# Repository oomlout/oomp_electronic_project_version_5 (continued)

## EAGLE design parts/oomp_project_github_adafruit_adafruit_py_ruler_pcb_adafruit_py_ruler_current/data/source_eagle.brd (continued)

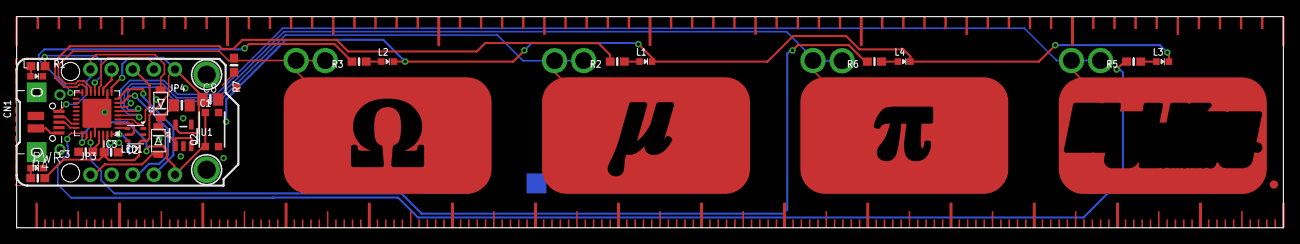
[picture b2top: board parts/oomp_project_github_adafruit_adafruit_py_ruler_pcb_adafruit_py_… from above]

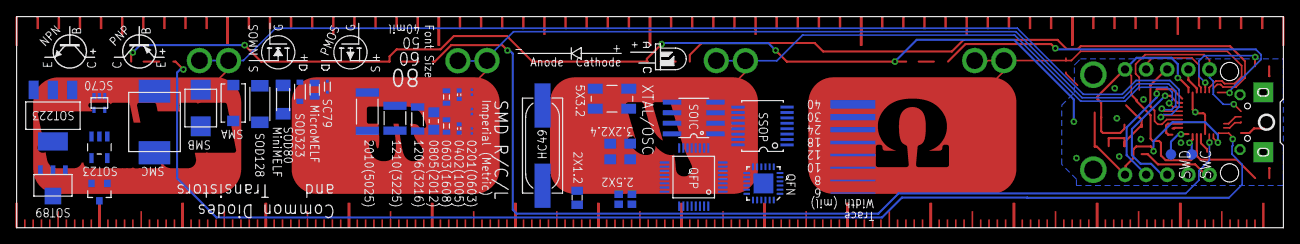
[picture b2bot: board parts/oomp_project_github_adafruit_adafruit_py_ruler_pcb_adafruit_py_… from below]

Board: 2 copper layers, 152.4 x 25.4 mm, 96 parts (43 on the bottom side), 30 nets.

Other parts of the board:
E$1, E$2, E$3, E$4, E$5, E$6, E$7, E$8, E$9, E$10, E$11, E$12, E$13, E$14, E$15: EDGE-MILLIMETERS
E$16, E$60, E$63: 0201
E$17, E$18, E$19, E$20, E$21, E$22: EDGE-INCHES-TENTH
E$23, E$61: 0402
E$24, E$62: 0603
E$25: 0805
E$26: 1206
E$27: 1210
E$28: 2010
E$31: SOT223
E$32: SOT89
E$33: SOT23-5
E$34: SOT23-3
E$35: SC70
E$36: CRYSTAL-SMD-5X3.2
E$37: CRYSTAL-SMD-3.2X2.5
E$38: CRYSTAL-SMD-2.5X2
E$39: HC49UP
E$40: XTAL-2X1.2
E$41: MICROMELF-R
E$42: SC79_INFINEON
E$43: SMA-DIODE
E$44: SMB-DIODE
E$45: SMC
E$47: SOD-128
E$48: SOD-323
E$49: SOD80C
E$50: NMOS-SYMB
E$51: PMOS-SYMB
E$52: DIODE-SYMB
E$53: LED-GUIDE
E$54: NPN-SYMB
E$55: QFN-24
E$56: TSSOP16
E$57: SO08
E$58: TQFP32-5MM
E$59: PNP-SYMB
U$2: PYRULER_BOTTOM
U$7: PCBFEAT-REV-040
U$14: PYRULER_TOP
U$20: TRINKET_M0_TOP

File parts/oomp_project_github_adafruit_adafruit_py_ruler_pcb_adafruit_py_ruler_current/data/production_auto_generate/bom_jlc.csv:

Comment,Designator,Footprint,LCSC Part #
,"E$16,E$60,E$63",Adafruit_PyRuler-import-fps:0201,
,"E$23,E$61",Adafruit_PyRuler-import-fps:0402,
,"E$24,E$62",Adafruit_PyRuler-import-fps:0603,
,E$25,Adafruit_PyRuler-import-fps:0805,
,E$26,Adafruit_PyRuler-import-fps:1206,
,E$27,Adafruit_PyRuler-import-fps:1210,
,"JP3,JP4",Adafruit_PyRuler-import-fps:1X05_ROUND_70,C42431835
,E$28,Adafruit_PyRuler-import-fps:2010,
,E$38,Adafruit_PyRuler-import-fps:CRYSTAL-SMD-2.5X2,
,E$37,Adafruit_PyRuler-import-fps:CRYSTAL-SMD-3.2X2.5,
,E$36,Adafruit_PyRuler-import-fps:CRYSTAL-SMD-5X3.2,
,E$52,Adafruit_PyRuler-import-fps:DIODE-SYMB,
,"E$17,E$18,E$19,E$20,E$21,E$22",Adafruit_PyRuler-import-fps:EDGE-INCHES-TENTH,
,"E$1,E$2,E$3,E$4,E$5,E$6,E$7,E$8,E$9,E$10,E$11,E$12,E$13,E$14,E$15",Adafruit_PyRuler-import-fps:EDGE-MILLIMETERS,
,E$39,Adafruit_PyRuler-import-fps:HC49UP,
,E$53,Adafruit_PyRuler-import-fps:LED-GUIDE,
,E$41,Adafruit_PyRuler-import-fps:MICROMELF-R,
,E$50,Adafruit_PyRuler-import-fps:NMOS-SYMB,
,E$54,Adafruit_PyRuler-import-fps:NPN-SYMB,
,U$7,Adafruit_PyRuler-import-fps:PCBFEAT-REV-040,
,E$51,Adafruit_PyRuler-import-fps:PMOS-SYMB,
,E$59,Adafruit_PyRuler-import-fps:PNP-SYMB,
,U$2,Adafruit_PyRuler-import-fps:PYRULER_BOTTOM,
,U$14,Adafruit_PyRuler-import-fps:PYRULER_TOP,
,E$55,Adafruit_PyRuler-import-fps:QFN-24,
,E$35,Adafruit_PyRuler-import-fps:SC70,
,E$42,Adafruit_PyRuler-import-fps:SC79_INFINEON,
,E$43,Adafruit_PyRuler-import-fps:SMA-DIODE,
,E$44,Adafruit_PyRuler-import-fps:SMB-DIODE,
,E$45,Adafruit_PyRuler-import-fps:SMC,
,E$57,Adafruit_PyRuler-import-fps:SO08,
,E$47,Adafruit_PyRuler-import-fps:SOD-128,
,E$48,Adafruit_PyRuler-import-fps:SOD-323,
,E$49,Adafruit_PyRuler-import-fps:SOD80C,
,E$31,Adafruit_PyRuler-import-fps:SOT223,
,E$34,Adafruit_PyRuler-import-fps:SOT23-3,
,E$33,Adafruit_PyRuler-import-fps:SOT23-5,
,E$32,Adafruit_PyRuler-import-fps:SOT89,
,E$58,Adafruit_PyRuler-import-fps:TQFP32-5MM,
,U$20,Adafruit_PyRuler-import-fps:TRINKET_M0_TOP,
,E$56,Adafruit_PyRuler-import-fps:TSSOP16,
,E$40,Adafruit_PyRuler-import-fps:XTAL-2X1.2,
10K,"R4,R5,R6",Adafruit_PyRuler-import-fps:0603-NO,C98220
10uF,"C1,C8",Adafruit_PyRuler-import-fps:0805-NO,
1uF,"C2,C3",Adafruit_PyRuler-import-fps:0603-NO,C5673
2.2K,"R1,R2,R3",Adafruit_PyRuler-import-fps:0603-NO,C4190
2M,R7,Adafruit_PyRuler-import-fps:0603-NO,
4U#20329,CN1,Adafruit_PyRuler-import-fps:4UCONN_20329_NARROW,
AP102-2020,LED1,Adafruit_PyRuler-import-fps:APA102_2020,
AP2112K-3.3,U1,Adafruit_PyRuler-import-fps:SOT23-5,
ATSAMD21E,IC3,Adafruit_PyRuler-import-fps:QFN32_5MM,
blue,L3,Adafruit_PyRuler-import-fps:CHIPLED_0603_NOOUTLINE,
FIDUCIAL_1MM,"U$1,U$6",Adafruit_PyRuler-import-fps:FIDUCIAL_1MM,
green,"L4,PWR0",Adafruit_PyRuler-import-fps:CHIPLED_0603_NOOUTLINE,
red,"L0,L2",Adafruit_PyRuler-import-fps:CHIPLED_0603_NOOUTLINE,
reset,Q2,Adafruit_PyRuler-import-fps:BTN_KMR2_4.6X2.8,
SCHOTTKY,"D2,D3",Adafruit_PyRuler-import-fps:SOD-123FL,
"TPB1,27","SWC0,SWD0","Adafruit_PyRuler-import-fps:B1,27",
yellow,L1,Adafruit_PyRuler-import-fps:CHIPLED_0603_NOOUTLINE,

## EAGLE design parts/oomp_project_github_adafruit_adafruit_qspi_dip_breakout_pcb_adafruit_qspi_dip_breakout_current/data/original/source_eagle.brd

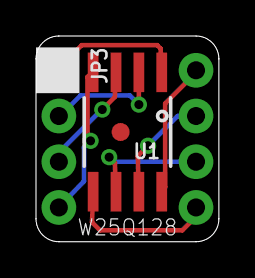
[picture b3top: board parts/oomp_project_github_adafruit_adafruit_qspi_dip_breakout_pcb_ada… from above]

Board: 2 copper layers, 10.2 x 11.4 mm, 5 parts (1 on the bottom side), 8 nets.

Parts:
FID1: FIDUCIAL_1MM
JP2, JP3: 1X04_ROUND_76
U1: GENERIC QSPI; SOIC8_208MIL
U$4: ADAFRUIT_2.5MM

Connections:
3.3V: JP2.1, U1.8
GND: JP3.4, U1.4
IO2: JP3.3, U1.3
IO3: JP2.2, U1.7
MISO: JP3.2, U1.2
MOSI: JP2.4, U1.5
SCK: JP2.3, U1.6
SS: JP3.1, U1.1

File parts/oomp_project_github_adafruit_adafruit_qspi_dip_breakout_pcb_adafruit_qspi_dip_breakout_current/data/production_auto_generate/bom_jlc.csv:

Comment,Designator,Footprint,LCSC Part #
,"JP2,JP3",Adafruit QSPI DIP Breakout-import-fps:1X04_ROUND_76,C42431795
,U$4,Adafruit QSPI DIP Breakout-import-fps:ADAFRUIT_2.5MM,
GENERIC QSPI,U1,Adafruit QSPI DIP Breakout-import-fps:SOIC8_208MIL,

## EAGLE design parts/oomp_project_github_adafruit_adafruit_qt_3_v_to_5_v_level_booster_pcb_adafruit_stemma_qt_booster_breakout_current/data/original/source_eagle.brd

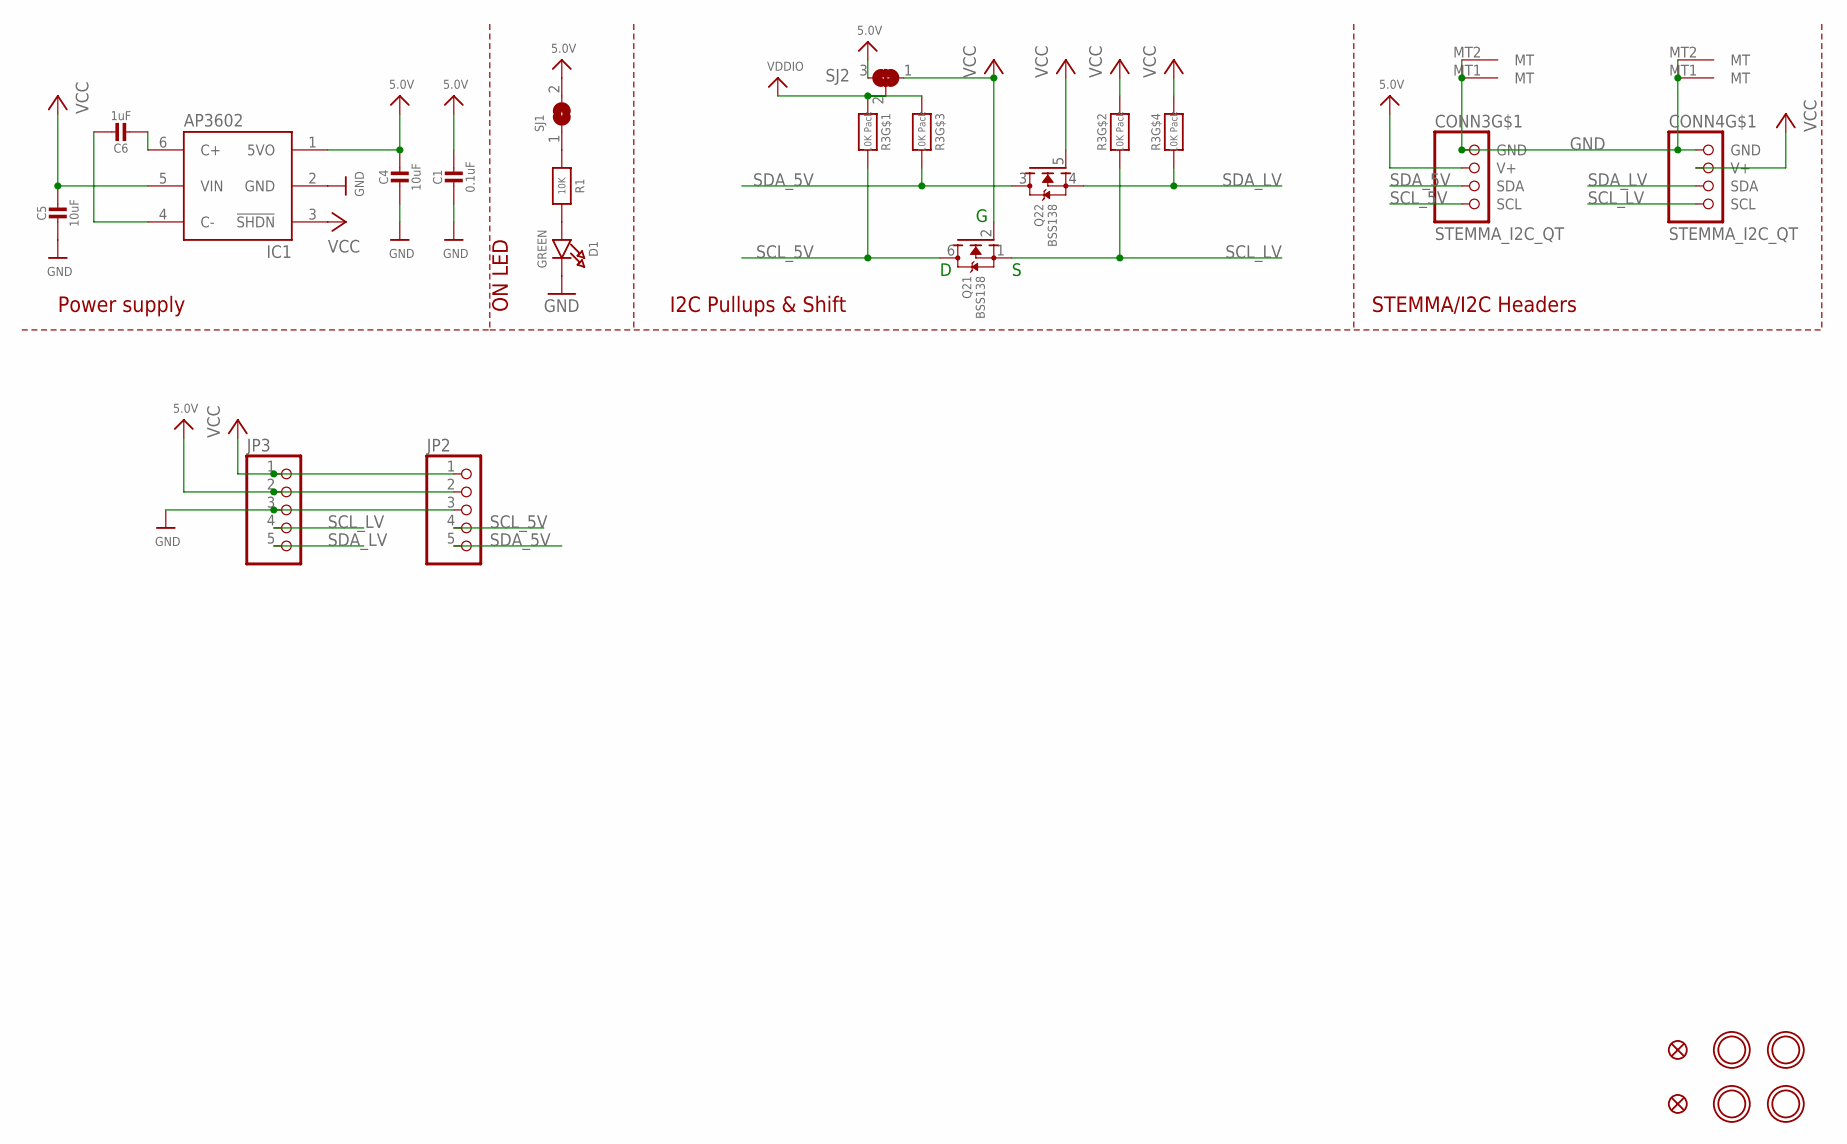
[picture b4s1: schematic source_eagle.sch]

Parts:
C1: 0.1uF; 0603-NO
C4, C5: 10uF; 0805-NO
C6: 1uF; 0805-NO
CONN3, CONN4: STEMMA_I2C_QT; JST_SH4
D1: GREEN; CHIPLED_0603_NOOUTLINE
FID3, FID4: FIDUCIAL_1MM
IC1: AP3602/RT9361; SOT23-6
JP2, JP3: HEADER-1X576MIL; 1X05_ROUND_76
Q2: BSS138; SOT363
R1: 10K; 0603-NO
R3: 10K Pack; RESPACK_4X0603
SJ1: SOLDERJUMPERCLOSED; SOLDERJUMPER_CLOSEDWIRE
SJ2: SOLDERJUMPER_2WAY; SOLDERJUMPER_2WAY_OPEN_NOPASTE
U$1, U$17, U$19, U$21: MOUNTINGHOLE2.5; MOUNTINGHOLE_2.5_PLATED

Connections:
5.0V: C1.1, C4.1, CONN3.2 (V+), IC1.1 (5VO), JP2.2, JP3.2, SJ1.2, SJ2.3
GND: C1.2, C4.2, C5.2, CONN3.1 (GND), CONN3.MT1 (MT), CONN3.MT2 (MT), CONN4.1 (GND), CONN4.MT1 (MT), CONN4.MT2 (MT), D1.C, IC1.2 (GND), JP2.3, JP3.3
unnamed: D1.A, R1.2
unnamed: R1.1, SJ1.1
unnamed: C6.2, IC1.6 (C+)
unnamed: C6.1, IC1.4 (C-)
SCL_5V: CONN3.4 (SCL), JP2.4, Q2.6 (D), R3.8 (2)
SCL_LV: CONN4.4 (SCL), JP3.4, Q2.1 (S), R3.7 (2)
SDA_5V: CONN3.3 (SDA), JP2.5, Q2.3 (D), R3.6 (2)
SDA_LV: CONN4.3 (SDA), JP3.5, Q2.4 (S), R3.5 (2)
VCC: C5.1, CONN4.2 (V+), IC1.3 (!SHDN), IC1.5 (VIN), JP2.1, JP3.1, Q2.2 (G), Q2.5 (G), R3.2 (1), R3.4 (1), SJ2.1
VDDIO: R3.1, R3.3 (1), SJ2.2

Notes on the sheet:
I2C Pullups & Shift
STEMMA/I2C Headers
ON LED
Power supply

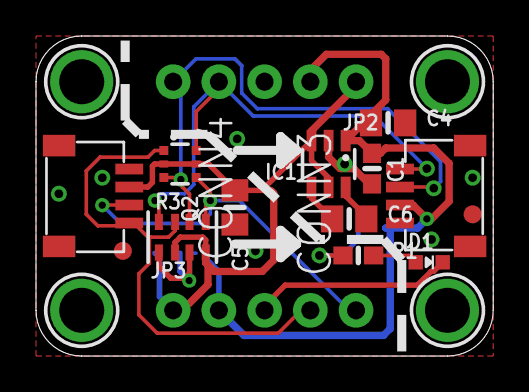
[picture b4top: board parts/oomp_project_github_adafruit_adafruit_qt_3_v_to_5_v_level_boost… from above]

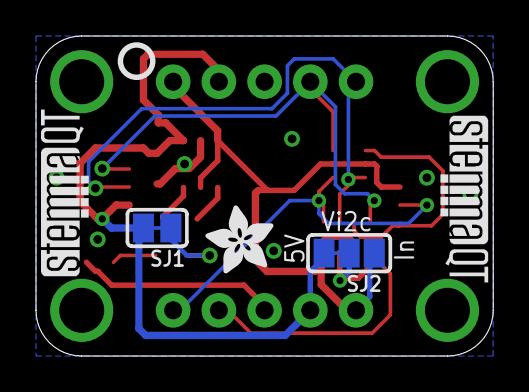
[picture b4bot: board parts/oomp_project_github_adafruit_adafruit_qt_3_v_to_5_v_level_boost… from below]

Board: 2 copper layers, 25.4 x 17.8 mm, 40 parts (8 on the bottom side), 12 nets.

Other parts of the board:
PLABEL0: PLABEL0
PLABEL1: PLABEL1
PLABEL2: PLABEL2
PLABEL3: PLABEL3
PLABEL4: PLABEL4
PLABEL5: PLABEL5
PLABEL6: PLABEL6
PLABEL7: PLABEL7
PLABEL8: PLABEL8
PLABEL9: PLABEL9
PLABEL10: PLABEL10
PLABEL11: PLABEL11
PLABEL12: PLABEL12
PLABEL13: PLABEL13
PLABEL14: PLABEL14
U$2: ADAFRUIT_3.5MM
U$25: PCBFEAT-REV-040
U$30, U$31: STEMMAQT

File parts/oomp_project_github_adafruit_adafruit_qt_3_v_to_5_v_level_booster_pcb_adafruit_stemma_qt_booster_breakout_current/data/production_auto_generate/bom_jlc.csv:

Comment,Designator,Footprint,LCSC Part #
,"JP2,JP3",Adafruit STEMMA QT Booster Breakout-import-fps:1X05_ROUND_76,C42431835
,U$2,Adafruit STEMMA QT Booster Breakout-import-fps:ADAFRUIT_3.5MM,
,U$25,Adafruit STEMMA QT Booster Breakout-import-fps:PCBFEAT-REV-040,
,PLABEL0,Adafruit STEMMA QT Booster Breakout-import-fps:PLABEL0,
,PLABEL1,Adafruit STEMMA QT Booster Breakout-import-fps:PLABEL1,
,PLABEL10,Adafruit STEMMA QT Booster Breakout-import-fps:PLABEL10,
,PLABEL11,Adafruit STEMMA QT Booster Breakout-import-fps:PLABEL11,
,PLABEL12,Adafruit STEMMA QT Booster Breakout-import-fps:PLABEL12,
,PLABEL13,Adafruit STEMMA QT Booster Breakout-import-fps:PLABEL13,
,PLABEL14,Adafruit STEMMA QT Booster Breakout-import-fps:PLABEL14,
,PLABEL2,Adafruit STEMMA QT Booster Breakout-import-fps:PLABEL2,
,PLABEL3,Adafruit STEMMA QT Booster Breakout-import-fps:PLABEL3,
,PLABEL4,Adafruit STEMMA QT Booster Breakout-import-fps:PLABEL4,
,PLABEL5,Adafruit STEMMA QT Booster Breakout-import-fps:PLABEL5,
,PLABEL6,Adafruit STEMMA QT Booster Breakout-import-fps:PLABEL6,
,PLABEL7,Adafruit STEMMA QT Booster Breakout-import-fps:PLABEL7,
,PLABEL8,Adafruit STEMMA QT Booster Breakout-import-fps:PLABEL8,
,PLABEL9,Adafruit STEMMA QT Booster Breakout-import-fps:PLABEL9,
,"U$30,U$31",Adafruit STEMMA QT Booster Breakout-import-fps:STEMMAQT,
0.1uF,C1,Adafruit STEMMA QT Booster Breakout-import-fps:0603-NO,C14663
10K,R1,Adafruit STEMMA QT Booster Breakout-import-fps:0603-NO,C98220
10K Pack,R3,Adafruit STEMMA QT Booster Breakout-import-fps:RESPACK_4X0603,C98220
10uF,"C4,C5",Adafruit STEMMA QT Booster Breakout-import-fps:0805-NO,
1uF,C6,Adafruit STEMMA QT Booster Breakout-import-fps:0805-NO,
AP3602/RT9361,IC1,Adafruit STEMMA QT Booster Breakout-import-fps:SOT23-6,
BSS138,Q2,Adafruit STEMMA QT Booster Breakout-import-fps:SOT363,
GREEN,D1,Adafruit STEMMA QT Booster Breakout-import-fps:CHIPLED_0603_NOOUTLINE,
STEMMA_I2C_QT,"CONN3,CONN4",Adafruit STEMMA QT Booster Breakout-import-fps:JST_SH4,C160404

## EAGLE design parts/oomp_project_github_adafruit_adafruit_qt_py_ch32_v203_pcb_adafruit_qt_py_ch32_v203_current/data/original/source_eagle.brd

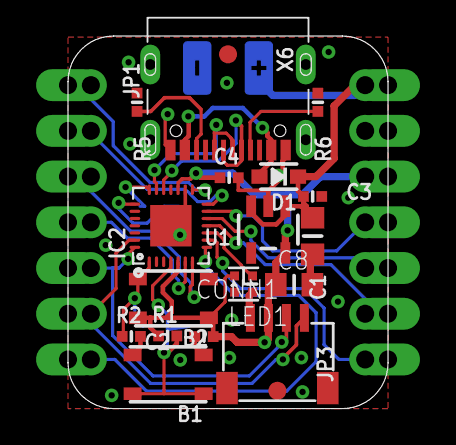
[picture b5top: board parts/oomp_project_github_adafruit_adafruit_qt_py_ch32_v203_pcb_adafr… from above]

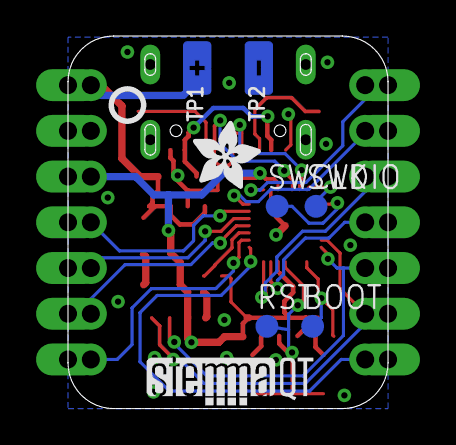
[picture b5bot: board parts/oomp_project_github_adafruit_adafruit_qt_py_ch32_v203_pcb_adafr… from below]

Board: 2 copper layers, 17.8 x 20.7 mm, 48 parts (26 on the bottom side), 24 nets.

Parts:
B1: BTN_RST; BTN_RKB2_4.6X2.8
B2: BTN_BOOT; BTN_RKB2_4.6X2.8
BOOT: TPB1,27; B1,27
C1, C8: 10uF; _0805MP
C2, C3, C4: 1uF; _0402NO
CONN1: STEMMA_I2C_QTSKINNY; JST_SH4_SKINNY
D1: NSR0320; SOD-323_MINI
IC2: CH32V203G6U6_; QFN28_4MM_0.4MM
JP1, JP3: 1X07_CASTEL
LED1: WS2812B_SK6805_1515; SK6805_1515
PLABEL0: PLABEL0
PLABEL1: PLABEL1
PLABEL2: PLABEL2
PLABEL3: PLABEL3
PLABEL4: PLABEL4
PLABEL5: PLABEL5
PLABEL6: PLABEL6
PLABEL7: PLABEL7
PLABEL8: PLABEL8
PLABEL9: PLABEL9
PLABEL10: PLABEL10
PLABEL11: PLABEL11
PLABEL12: PLABEL12
PLABEL13: PLABEL13
PLABEL14: PLABEL14
PLABEL15: PLABEL15
R1, R2: 10K; _0402NO
R5, R6: 5.1K; _0402NO
RST: TPB1,27; B1,27
SWCLK: SWCLK; B1,27
SWDIO: SWDIO; B1,27
TP1: TESTPOINT_PLUS_1X3MM
TP2: TESTPOINT_MINUS_1X3MM
U1: AP2112K-3.3; SOT23-5
U$6, U$8: FIDUCIAL_1MM
U$11: ADAFRUIT_3.5MM
U$12: PCBFEAT-REV-040
U$13: QTPY_CH32V203_BOT
U$21: STEMMAQT
U$23: QTPY_CH32V203_TOP
X6: USB TYPE C; USB_C_CUSB31-CFM2AX-01-X

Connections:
3.3V: B2.A, B2.A', C2.1, C4.1, C8.1, CONN1.2, IC2.5, IC2.17, JP3.5, JP3.5C, LED1.2, R1.1, U1.5
!RESET: B1.A, B1.A', IC2.4, R1.2, RST.TP
+5V: C1.1, C3.1, D1.C, JP3.7, JP3.7C, TP1.P$1, U1.1, U1.3
A0: IC2.15, JP1.1, JP1.1C
A1: IC2.14, JP1.2, JP1.2C
A2: IC2.7, JP1.3, JP1.3C
A3: IC2.6, JP1.4, JP1.4C
BOOT0: B2.B, BOOT.TP, IC2.1, R2.1
CC1: R6.2, X6.A5
CC2: R5.2, X6.B5
D+: IC2.20, X6.A6, X6.B6
D-: IC2.19, X6.A7, X6.B7
GND: B1.B, B1.B', C1.2, C2.2, C3.2, C4.2, C8.2, CONN1.1, CONN1.MT1, CONN1.MT2, IC2.16, IC2.THERMAL, JP3.6, JP3.6C, LED1.4, R2.2, R5.1, R6.1, TP2.P$1, U1.2, X6.A1B12, X6.B1A12
MISO: IC2.12, JP3.3, JP3.3C
MOSI: IC2.13, JP3.4, JP3.4C
NEOPIX: IC2.10, LED1.1
RX: IC2.9, JP3.1, JP3.1C
SCK: IC2.11, JP3.2, JP3.2C
SCL: CONN1.4, IC2.27, JP1.6, JP1.6C
SDA: CONN1.3, IC2.28, JP1.5, JP1.5C
SWC: IC2.22, SWCLK.TP
SWD: IC2.21, SWDIO.TP
TX: IC2.8, JP1.7, JP1.7C
VBUS: D1.A, X6.A4B9, X6.B4A9

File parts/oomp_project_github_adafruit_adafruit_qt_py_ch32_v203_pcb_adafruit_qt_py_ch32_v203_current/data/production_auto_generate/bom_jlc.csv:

Comment,Designator,Footprint,LCSC Part #
,"JP1,JP3",Adafruit QT Py CH32V203-import-fps:1X07_CASTEL,C7501585
,U$11,Adafruit QT Py CH32V203-import-fps:ADAFRUIT_3.5MM,
,U$12,Adafruit QT Py CH32V203-import-fps:PCBFEAT-REV-040,
,PLABEL0,Adafruit QT Py CH32V203-import-fps:PLABEL0,
,PLABEL1,Adafruit QT Py CH32V203-import-fps:PLABEL1,
,PLABEL10,Adafruit QT Py CH32V203-import-fps:PLABEL10,
,PLABEL11,Adafruit QT Py CH32V203-import-fps:PLABEL11,
,PLABEL12,Adafruit QT Py CH32V203-import-fps:PLABEL12,
,PLABEL13,Adafruit QT Py CH32V203-import-fps:PLABEL13,
,PLABEL14,Adafruit QT Py CH32V203-import-fps:PLABEL14,
,PLABEL15,Adafruit QT Py CH32V203-import-fps:PLABEL15,
,PLABEL2,Adafruit QT Py CH32V203-import-fps:PLABEL2,
,PLABEL3,Adafruit QT Py CH32V203-import-fps:PLABEL3,
,PLABEL4,Adafruit QT Py CH32V203-import-fps:PLABEL4,
,PLABEL5,Adafruit QT Py CH32V203-import-fps:PLABEL5,
,PLABEL6,Adafruit QT Py CH32V203-import-fps:PLABEL6,
,PLABEL7,Adafruit QT Py CH32V203-import-fps:PLABEL7,
,PLABEL8,Adafruit QT Py CH32V203-import-fps:PLABEL8,
,PLABEL9,Adafruit QT Py CH32V203-import-fps:PLABEL9,
,U$13,Adafruit QT Py CH32V203-import-fps:QTPY_CH32V203_BOT,
,U$23,Adafruit QT Py CH32V203-import-fps:QTPY_CH32V203_TOP,
,U$21,Adafruit QT Py CH32V203-import-fps:STEMMAQT,
,TP2,Adafruit QT Py CH32V203-import-fps:TESTPOINT_MINUS_1X3MM,
,TP1,Adafruit QT Py CH32V203-import-fps:TESTPOINT_PLUS_1X3MM,
10K,"R1,R2",Adafruit QT Py CH32V203-import-fps:_0402NO,C2906861
10uF,"C1,C8",Adafruit QT Py CH32V203-import-fps:_0805MP,
1uF,"C2,C3,C4",Adafruit QT Py CH32V203-import-fps:_0402NO,C2887021
5.1K,"R5,R6",Adafruit QT Py CH32V203-import-fps:_0402NO,C25905
AP2112K-3.3,U1,Adafruit QT Py CH32V203-import-fps:SOT23-5,
BTN_BOOT,B2,Adafruit QT Py CH32V203-import-fps:BTN_RKB2_4.6X2.8,
BTN_RST,B1,Adafruit QT Py CH32V203-import-fps:BTN_RKB2_4.6X2.8,
CH32V203G6U6_,IC2,Adafruit QT Py CH32V203-import-fps:QFN28_4MM_0.4MM,
FIDUCIAL_1MM,"U$6,U$8",Adafruit QT Py CH32V203-import-fps:FIDUCIAL_1MM,
NSR0320,D1,Adafruit QT Py CH32V203-import-fps:SOD-323_MINI,
STEMMA_I2C_QTSKINNY,CONN1,Adafruit QT Py CH32V203-import-fps:JST_SH4_SKINNY,
SWCLK,SWCLK0,"Adafruit QT Py CH32V203-import-fps:B1,27",
SWDIO,SWDIO0,"Adafruit QT Py CH32V203-import-fps:B1,27",
"TPB1,27","BOOT0,RST0","Adafruit QT Py CH32V203-import-fps:B1,27",
USB TYPE C,X6,Adafruit QT Py CH32V203-import-fps:USB_C_CUSB31-CFM2AX-01-X,
WS2812B_SK6805_1515,LED1,Adafruit QT Py CH32V203-import-fps:SK6805_1515,

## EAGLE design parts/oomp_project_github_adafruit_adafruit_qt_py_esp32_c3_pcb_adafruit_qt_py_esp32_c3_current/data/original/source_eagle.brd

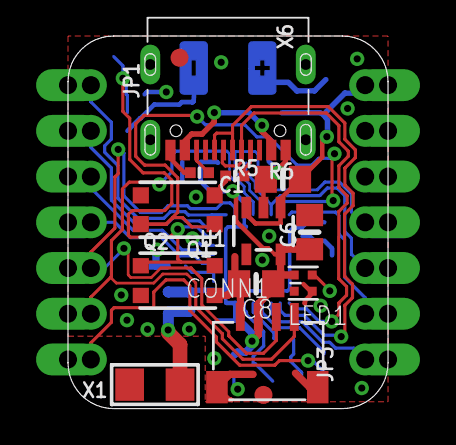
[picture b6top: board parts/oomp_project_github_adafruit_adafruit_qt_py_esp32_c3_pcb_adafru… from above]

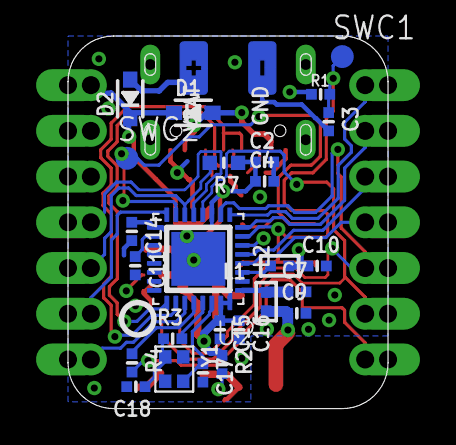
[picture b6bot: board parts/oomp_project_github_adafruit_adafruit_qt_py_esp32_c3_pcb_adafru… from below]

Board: 2 copper layers, 17.8 x 20.7 mm, 46 parts (29 on the bottom side), 31 nets.

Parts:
C1, C6, C8: 22uF; 0805-NO
C2, C3, C11, C15: 1uF; _0402NO
C4, C10, C14: 0.1uF; _0402NO
C7, C9: TBD; _0402NO
C16: 0.01uF; _0402NO
C17, C18: 16pF; _0402NO
CONN1: STEMMA_I2C_QTSKINNY; JST_SH4_SKINNY
D1, D2: NSR0320; SOD-323_MINI
GND: TESTPOINT_MINUS_1X3MM
JP1, JP3: 1X07_CASTEL
L1: 2nH; _0402
L2: 0 ohm; _0402
LED1: WS2812B_SK6805_1515; SK6805_1515
Q1: BOOT0; BTN_KMR2_4.6X2.8
Q2: reset; BTN_KMR2_SLIM
R1, R2: 10K; _0402NO
R3: 0; _0402NO
R4: 1k; _0402NO
R5, R6: 5.1K; _0402NO
R7: 10K; _0603MP_TWO6MIL
SWC1, SWC2: TPB1,27; B1,27
U1: AP2112K-3.3; SOT23-5
U2: ESP32-C3FH4; QFN32_5MM
U$3: QTPYC3_TOP
U$6, U$8: FIDUCIAL_1MM
U$12: PCBFEAT-REV-040
U$18: QTPYC3_BOT
VBAT: TESTPOINT_PLUS_1X3MM
X1: 2.4GHz; ANT_2450AT18B100
X6: USB TYPE C; USB_C_CUSB31-CFM2AX-01-X
Y1: 40MHz; CRYSTAL_2X1.6

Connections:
3.3V: C2.1, C4.1, C6.1, C8.1, C10.1, C14.1, C15.1, C16.1, CONN1.2, JP3.5, JP3.5C, L1.1, LED1.2, R1.1, R2.1, R7.1, U1.5, U2.11, U2.17, U2.31, U2.32
!RESET: C3.1, Q2.A, Q2.A', R1.2, SWC1.TP, U2.7
+5V: C1.1, D1.C, D2.C, JP3.7, JP3.7C, U1.1, U1.3
A0: JP1.1, JP1.1C, U2.9
A1: JP1.2, JP1.2C, U2.8
A2: JP1.3, JP1.3C, U2.5
A3: JP1.4, JP1.4C, U2.4
BOOT: Q1.A, Q1.A', SWC2.TP, U2.15
CC1: R6.2, X6.A5
CC2: R5.2, X6.B5
D+: U2.26, X6.A6, X6.B6
D-: U2.25, X6.A7, X6.B7
GND: C1.2, C2.2, C3.2, C4.2, C6.2, C7.2, C8.2, C9.2, C10.2, C11.2, C14.2, C15.2, C16.2, C17.2, C18.2, CONN1.1, CONN1.MT1, CONN1.MT2, GND.P$1, JP3.6, JP3.6C, LED1.4, Q1.B', Q2.B, Q2.B', R5.1, R6.1, U1.2, U2.33, X6.A1B12, X6.B1A12
LNA: C7.1, L2.2, U2.1
MISO: JP3.3, JP3.3C, R7.2, U2.14
MOSI: JP3.4, JP3.4C, U2.13
unnamed: R4.1, U2.28
unnamed: C9.1, L2.1, X1.FP
unnamed: R3.2, U2.29
unnamed: C17.1, U2.30, Y1.3
unnamed: C18.1, R3.1, Y1.1
NEOPIX: LED1.1, R2.2, U2.6
RX: JP3.1, JP3.1C, U2.27
SCK: JP3.2, JP3.2C, U2.16
SCL: CONN1.4, JP1.6, JP1.6C, U2.12
SDA: CONN1.3, JP1.5, JP1.5C, U2.10
TX: JP1.7, JP1.7C, R4.2
VBAT: D2.A, VBAT.P$1
VBUS: D1.A, X6.A4B9, X6.B4A9
VDD3P3: L1.2, U2.2, U2.3
VDD_SPI: C11.1, U2.18

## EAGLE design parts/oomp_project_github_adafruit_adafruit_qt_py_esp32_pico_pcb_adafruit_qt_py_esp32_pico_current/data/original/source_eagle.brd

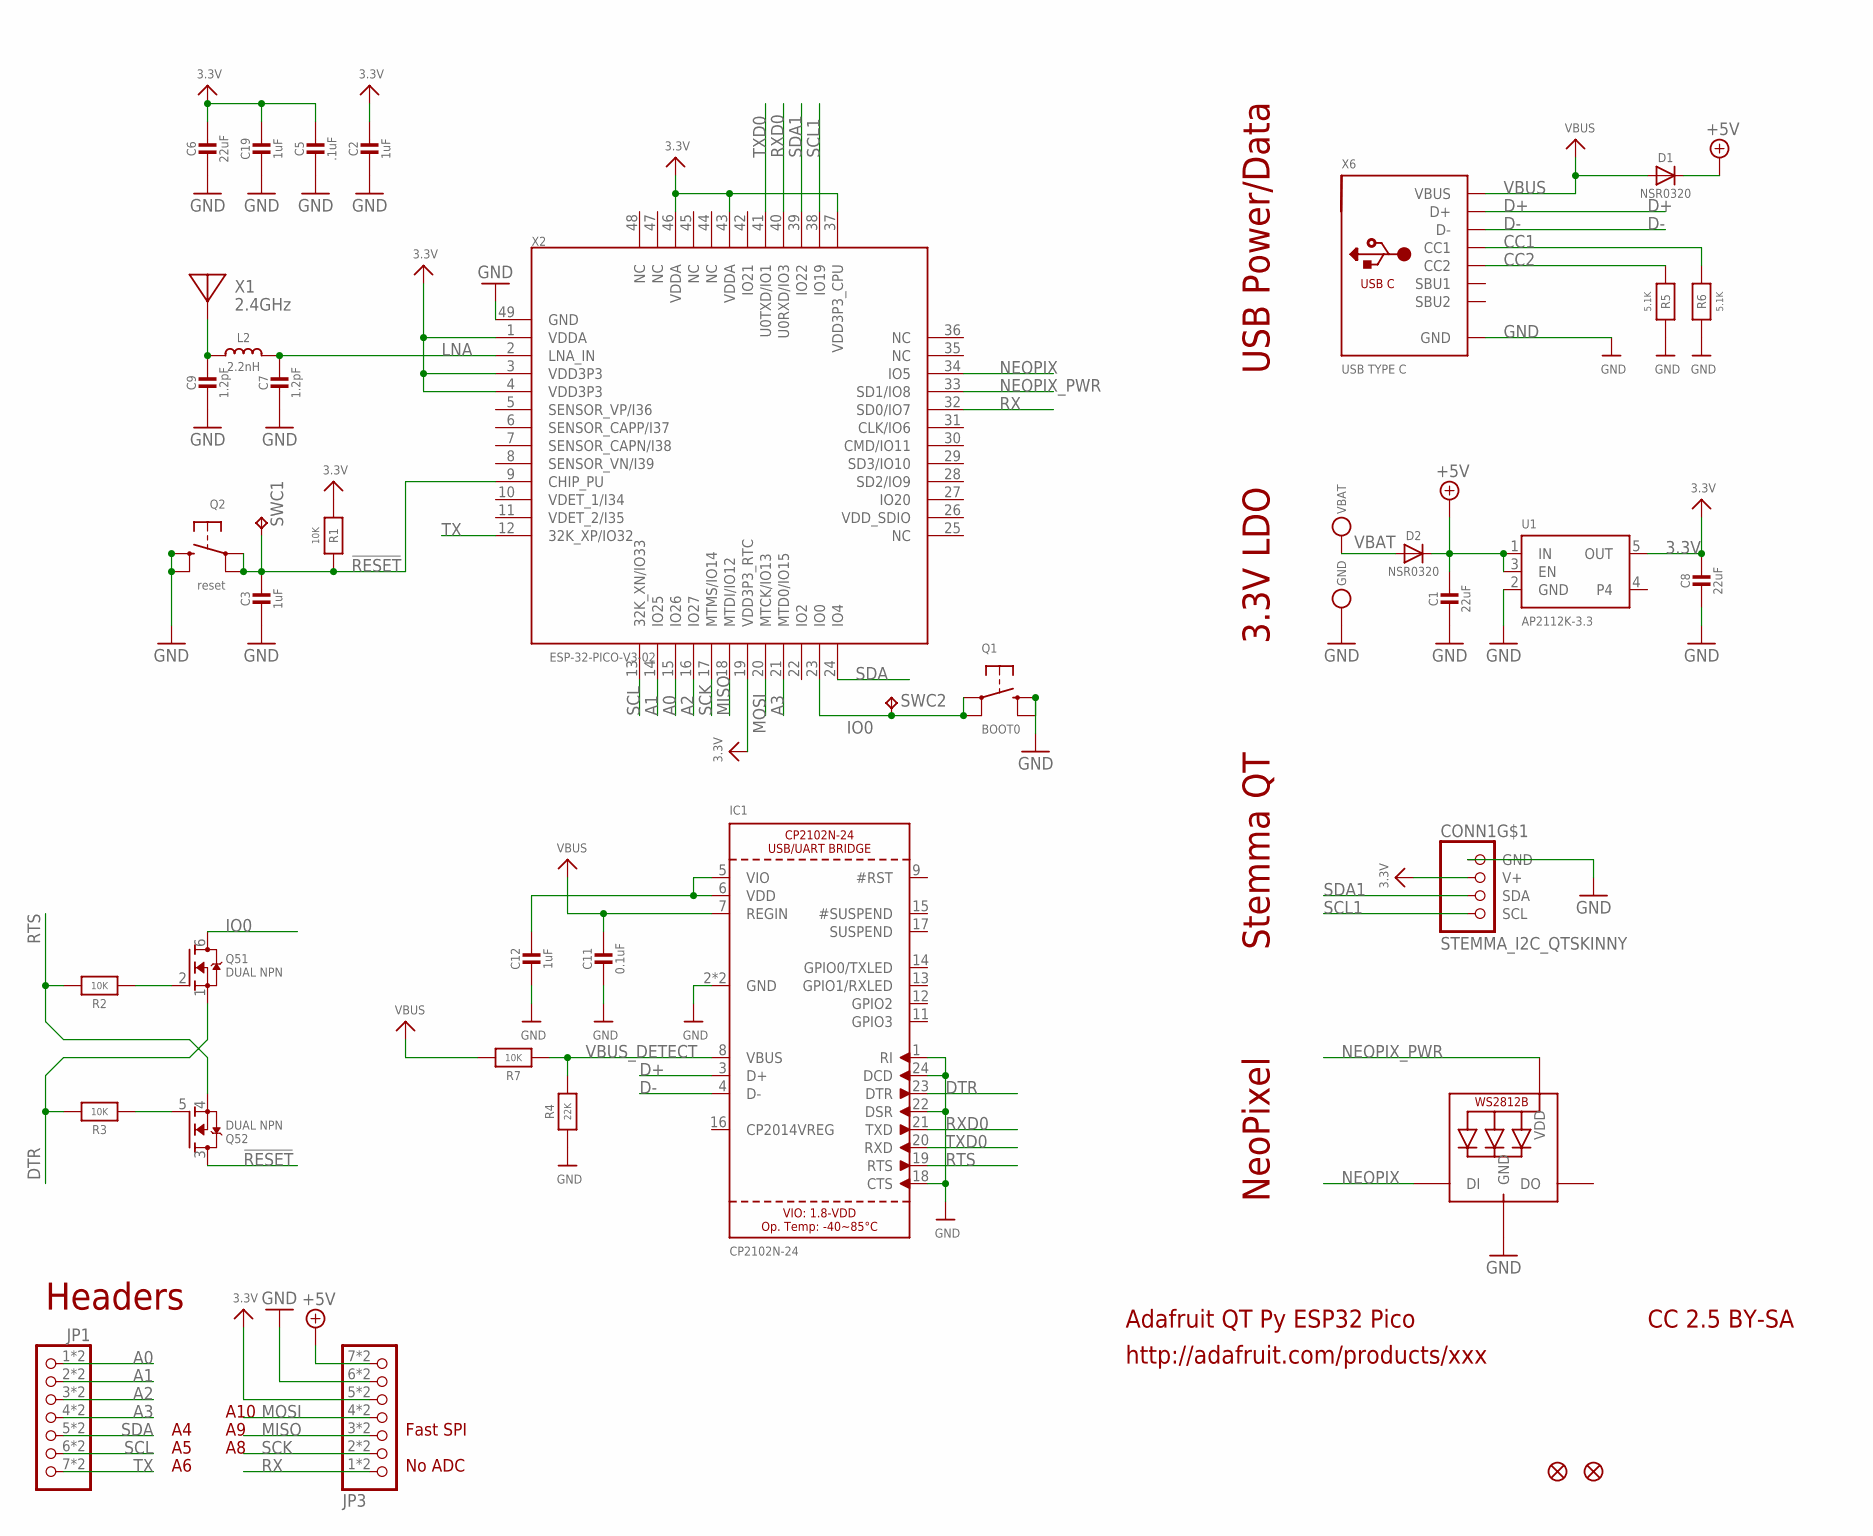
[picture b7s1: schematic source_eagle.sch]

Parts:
C1, C6, C8: 22uF; 0805-NO
C2, C3, C12: 1uF; _0402NO
C5: .1uF; _0402NO
C7, C9: 1.2pF; _0402NO
C11: 0.1uF; _0402NO
C19: 1uF; 0603-NO_WIDE
CONN1: STEMMA_I2C_QTSKINNY; JST_SH4_SKINNY
D1, D2: NSR0320; SOD-323_MINI
GND: TESTPOINT_MINUS; TESTPOINT_MINUS_1X3MM
IC1: CP2102N-24; QFN24_4MM_SMSC
JP1, JP3: HEADER-1X7_CASTEL; 1X07_CASTEL
L2: 2.2nH; _0402
LED1: WS2812B_SK6805_1515; SK6805_1515
Q1: BOOT0; BTN_KMR2_4.6X2.8
Q2: reset; BTN_KMR2_4.6X2.8
Q5: DUAL NPN; SOT363
R1, R2, R3, R7: 10K; _0402NO
R4: 22K; _0402NO
R5, R6: 5.1K; _0402NO
SWC1, SWC2: TPB1,27; B1,27
U1: AP2112K-3.3; SOT23-5
U$6, U$8: FIDUCIAL_1MM
VBAT: TESTPOINT_PLUS13; TESTPOINT_PLUS_1X3MM
X1: 2.4GHz; ANT_2450AT18B100
X2: ESP-32-PICO-V3-02; QFN48_7X7
X6: USB TYPE C; USB_C_CUSB31-CFM2AX-01-X

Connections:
3.3V: C2.1, C5.1, C6.1, C8.1, C19.1, CONN1.2 (V+), JP3.5, JP3.5C (5), R1.1, U1.5 (OUT), X2.1 (VDDA), X2.3 (VDD3P3), X2.4 (VDD3P3), X2.19 (VDD3P3_RTC), X2.37 (VDD3P3_CPU), X2.43 (VDDA), X2.46 (VDDA)
!RESET: C3.1, Q2.A, Q2.A' (P1), Q5.3 (D), R1.2, SWC1.TP, X2.9 (CHIP_PU)
+5V: C1.1, D1.C, D2.C, JP3.7, JP3.7C (7), U1.1 (IN), U1.3 (EN)
A0: JP1.1, JP1.1C (1), X2.15 (IO26)
A1: JP1.2, JP1.2C (2), X2.14 (IO25)
A2: JP1.3, JP1.3C (3), X2.16 (IO27)
A3: JP1.4, JP1.4C (4), X2.21 (MTD0/IO15)
CC1: R6.2, X6.A5 (CC1)
CC2: R5.2, X6.B5 (CC2)
D+: IC1.3 (D+), X6.A6 (D+), X6.B6 (D+)
D-: IC1.4 (D-), X6.A7 (D-), X6.B7 (D-)
DTR: IC1.23 (DTR), Q5.1 (S), R3.2
GND: C1.2, C2.2, C3.2, C5.2, C6.2, C7.2, C8.2, C9.2, C11.2, C12.2, C19.2, CONN1.1 (GND), GND.P$1, IC1.1 (RI), IC1.2 (GND), IC1.18 (CTS), IC1.22 (DSR), IC1.24 (DCD), IC1.THERM (GND), JP3.6, JP3.6C (6), LED1.4 (GND), Q1.B (S), Q1.B' (S1), Q2.B (S), Q2.B' (S1), R4.1, R5.1, R6.1, U1.2 (GND), X2.49 (GND), X6.A1B12 (GND), X6.B1A12 (GND)
IO0: Q1.A, Q1.A' (P1), Q5.6 (D), SWC2.TP, X2.23 (IO0)
LNA: C7.1, L2.2, X2.2 (LNA_IN)
MISO: JP3.3, JP3.3C (3), X2.18 (MTDI/IO12)
MOSI: JP3.4, JP3.4C (4), X2.20 (MTCK/IO13)
unnamed: C12.1, IC1.5 (VIO), IC1.6 (VDD)
unnamed: C9.1, L2.1, X1.FP
unnamed: Q5.5 (G), R3.1
unnamed: Q5.2 (G), R2.1
NEOPIX: LED1.1 (DI), X2.34 (IO5)
NEOPIX_PWR: LED1.2 (VDD), X2.33 (SD1/IO8)
RTS: IC1.19 (RTS), Q5.4 (S), R2.2
RX: JP3.1, JP3.1C (1), X2.32 (SD0/IO7)
RXD0: IC1.21 (TXD), X2.40 (U0RXD/IO3)
SCK: JP3.2, JP3.2C (2), X2.17 (MTMS/IO14)
SCL: JP1.6, JP1.6C (6), X2.13 (32K_XN/IO33)
SCL1: CONN1.4 (SCL), X2.38 (IO19)
SDA: JP1.5, JP1.5C (5), X2.24 (IO4)
SDA1: CONN1.3 (SDA), X2.39 (IO22)
TX: JP1.7, JP1.7C (7), X2.12 (32K_XP/IO32)
TXD0: IC1.20 (RXD), X2.41 (U0TXD/IO1)
VBAT: D2.A, VBAT.P$1
VBUS: C11.1, D1.A, IC1.7 (REGIN), R7.2, X6.A4B9 (VBUS), X6.B4A9 (VBUS)
VBUS_DETECT: IC1.8 (VBUS), R4.2, R7.1

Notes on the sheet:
Adafruit QT Py ESP32 Pico
http://adafruit.com/products/xxx
CC 2.5 BY-SA
NeoPixel
Stemma QT
3.3V LDO
USB Power/Data
Headers
Fast SPI
No ADC
A10

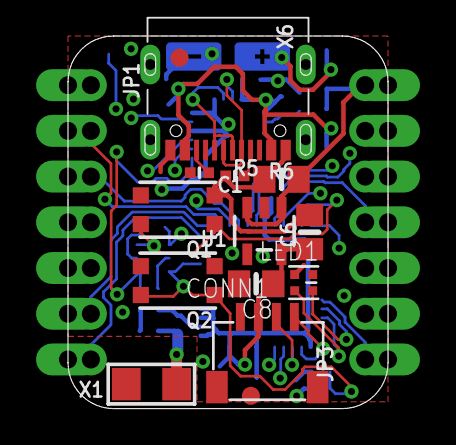
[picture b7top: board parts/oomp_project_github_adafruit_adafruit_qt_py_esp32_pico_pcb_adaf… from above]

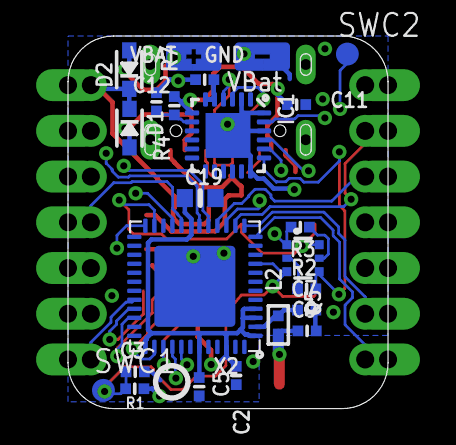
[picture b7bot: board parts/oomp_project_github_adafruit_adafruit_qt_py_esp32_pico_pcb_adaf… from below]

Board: 4 copper layers, 17.8 x 20.7 mm, 42 parts (25 on the bottom side), 36 nets.

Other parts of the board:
U$3: QTPY_ESP32_BOT
U$12: PCBFEAT-REV-040
U$22: QTPY_ESP32_TOP

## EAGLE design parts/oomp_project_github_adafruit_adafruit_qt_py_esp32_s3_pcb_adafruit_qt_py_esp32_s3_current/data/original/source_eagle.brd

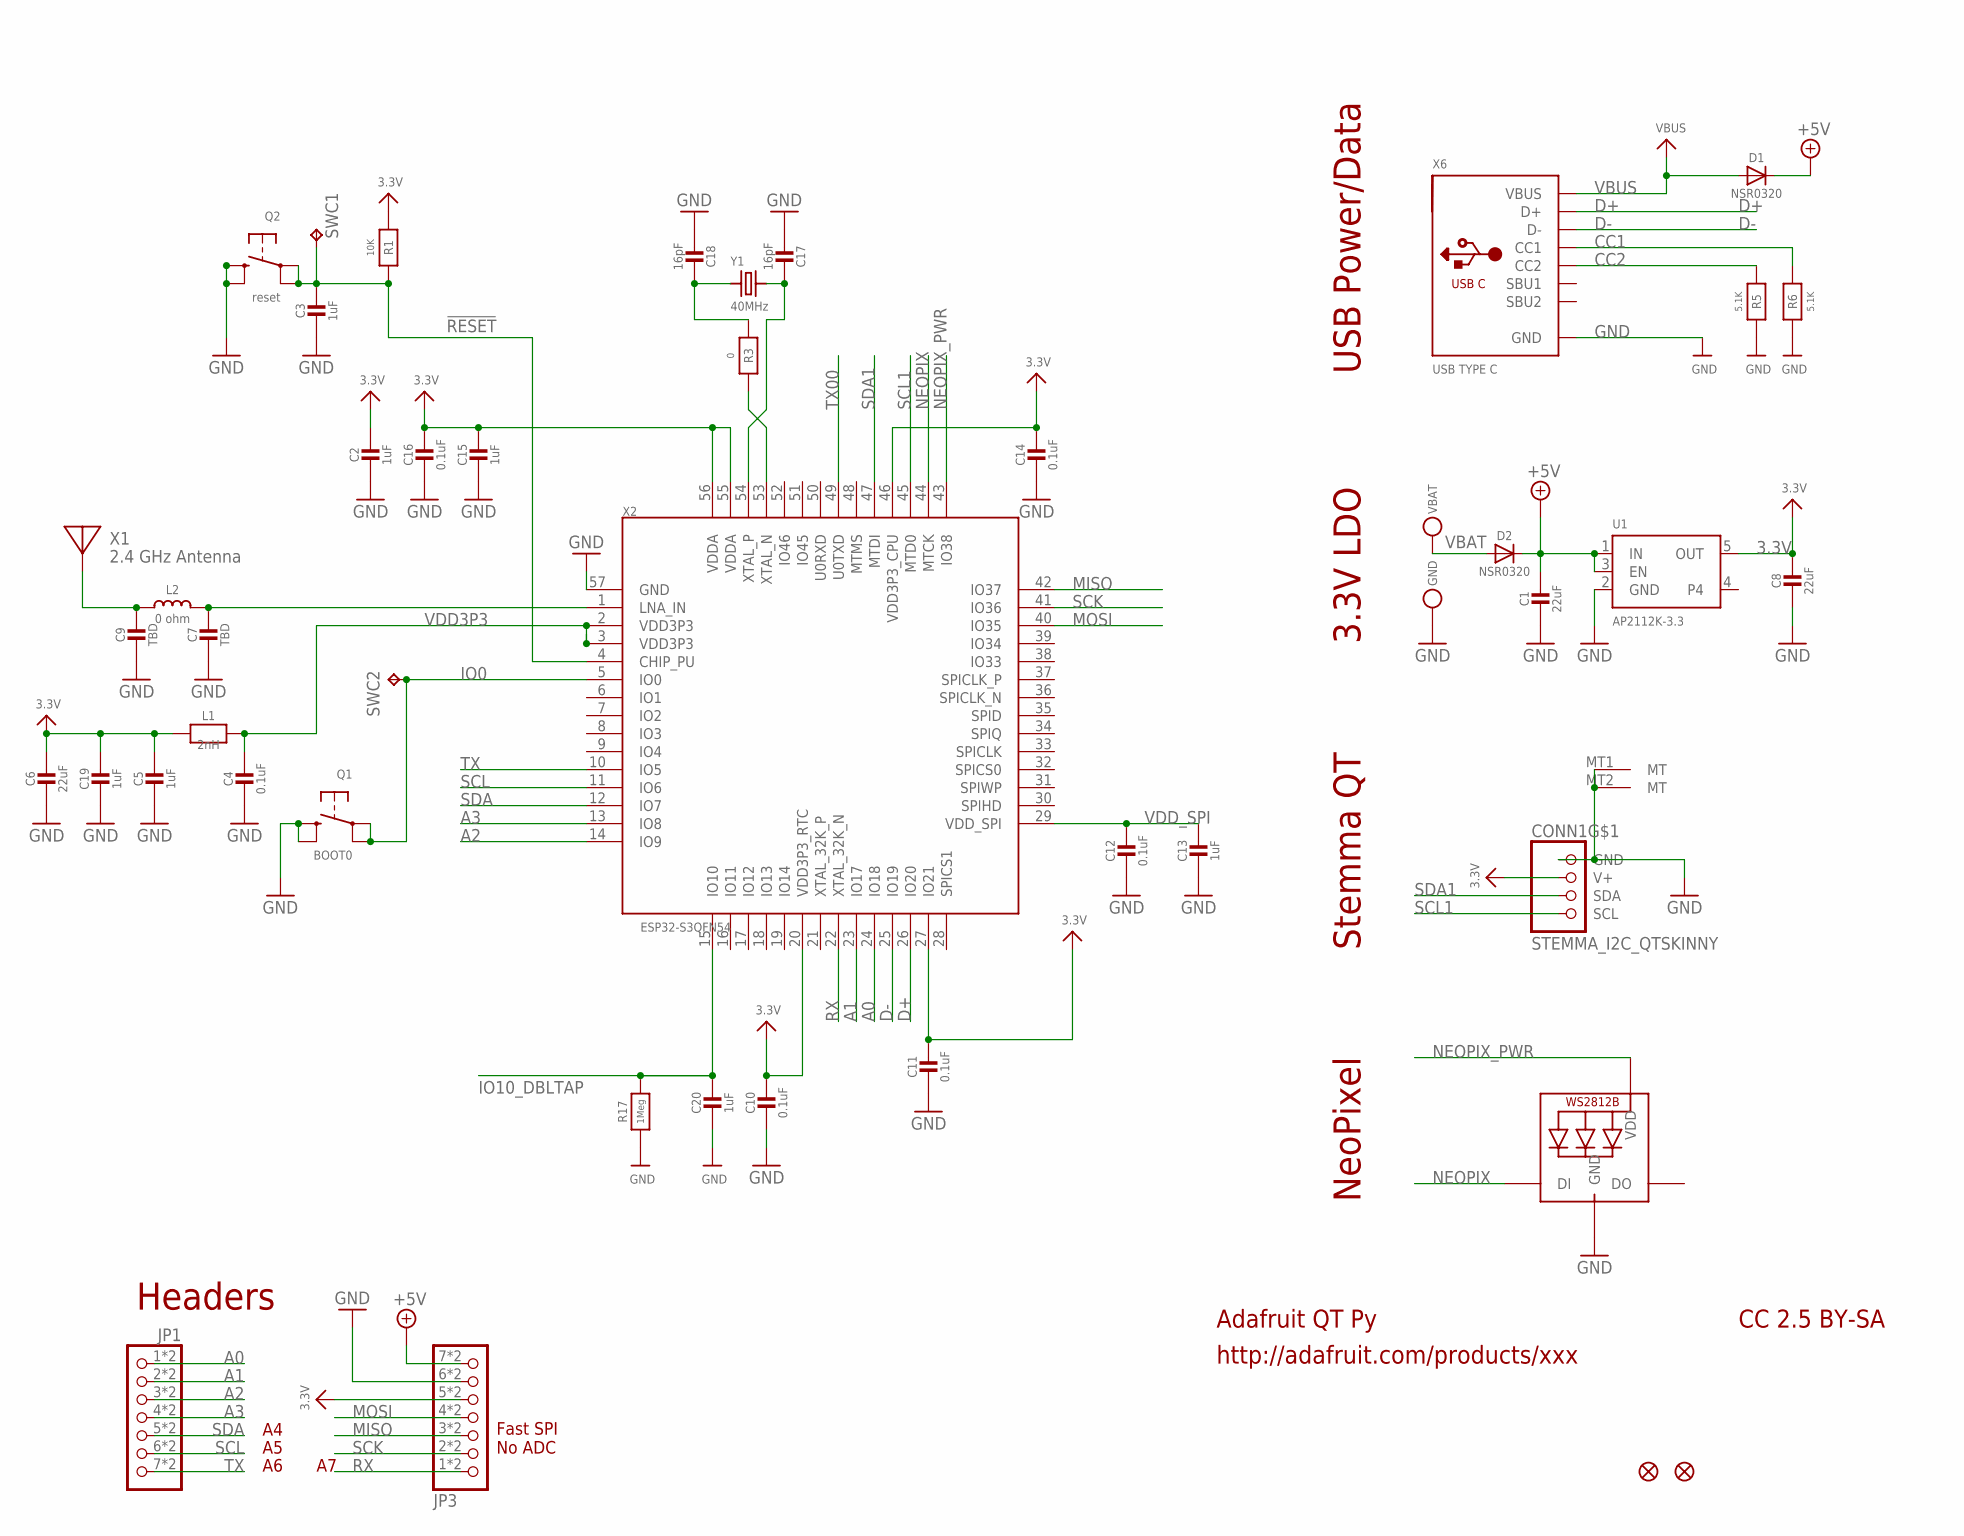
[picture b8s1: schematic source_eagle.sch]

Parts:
C1, C6, C8: 22uF; 0805-NO
C2, C3, C5, C13, C15, C19, C20: 1uF; _0402NO
C4, C10, C11, C12, C14, C16: 0.1uF; _0402NO
C7, C9: TBD; _0402NO
C17, C18: 16pF; _0402NO
CONN1: STEMMA_I2C_QTSKINNY; JST_SH4_SKINNY
D1, D2: NSR0320; SOD-323_MINI
GND: TESTPOINT_MINUS; TESTPOINT_MINUS_1X3MM
JP1, JP3: HEADER-1X7_CASTEL; 1X07_CASTEL
L1: 2nH; _0402NO
L2: 0 ohm; _0402
LED1: WS2812B_SK6805_1515; SK6805_1515
Q1: BOOT0; BTN_KMR2_4.6X2.8
Q2: reset; BTN_KMR2_4.6X2.8
R1: 10K; _0402NO
R3: 0; _0402NO
R5, R6: 5.1K; _0402NO
R17: 1Meg; _0402NO
SWC1, SWC2: TPB1,27; B1,27
U1: AP2112K-3.3; SOT23-5
U$6, U$8: FIDUCIAL_1MM
VBAT: TESTPOINT_PLUS13; TESTPOINT_PLUS_1X3MM
X1: 2.4 GHz Antenna; ANT_2450AT18B100
X2: ESP32-S3QFN54; QFN56_7X7
X6: USB TYPE C; USB_C_CUSB31-CFM2AX-01-X
Y1: 40MHz; CRYSTAL_2X1.6

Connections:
3.3V: C2.1, C5.1, C6.1, C8.1, C10.1, C11.1, C14.1, C15.1, C16.1, C19.1, CONN1.2 (V+), JP3.5, JP3.5C (5), L1.1, R1.1, U1.5 (OUT), X2.20 (VDD3P3_RTC), X2.27 (IO21), X2.46 (VDD3P3_CPU), X2.55 (VDDA), X2.56 (VDDA)
!RESET: C3.1, Q2.A, Q2.A' (P1), R1.2, SWC1.TP, X2.4 (CHIP_PU)
+5V: C1.1, D1.C, D2.C, JP3.7, JP3.7C (7), U1.1 (IN), U1.3 (EN)
A0: JP1.1, JP1.1C (1), X2.24 (IO18)
A1: JP1.2, JP1.2C (2), X2.23 (IO17)
A2: JP1.3, JP1.3C (3), X2.14 (IO9)
A3: JP1.4, JP1.4C (4), X2.13 (IO8)
CC1: R6.2, X6.A5 (CC1)
CC2: R5.2, X6.B5 (CC2)
D+: X2.26 (IO20), X6.A6 (D+), X6.B6 (D+)
D-: X2.25 (IO19), X6.A7 (D-), X6.B7 (D-)
GND: C1.2, C2.2, C3.2, C4.2, C5.2, C6.2, C7.2, C8.2, C9.2, C10.2, C11.2, C12.2, C13.2, C14.2, C15.2, C16.2, C17.2, C18.2, C19.2, C20.2, CONN1.1 (GND), CONN1.MT1 (MT), CONN1.MT2 (MT), GND.P$1, JP3.6, JP3.6C (6), LED1.4 (GND), Q1.B (S), Q1.B' (S1), Q2.B (S), Q2.B' (S1), R5.1, R6.1, R17.1, U1.2 (GND), X2.57 (GND), X6.A1B12 (GND), X6.B1A12 (GND)
IO0: Q1.A, Q1.A' (P1), SWC2.TP, X2.5 (IO0)
IO10_DBLTAP: C20.1, R17.2, X2.15 (IO10)
MISO: JP3.3, JP3.3C (3), X2.42 (IO37)
MOSI: JP3.4, JP3.4C (4), X2.40 (IO35)
unnamed: R3.2, X2.53 (XTAL_N)
unnamed: C7.1, L2.2, X2.1 (LNA_IN)
unnamed: C9.1, L2.1, X1.FP
unnamed: C17.1, X2.54 (XTAL_P), Y1.3 (2)
unnamed: C18.1, R3.1, Y1.1
NEOPIX: LED1.1 (DI), X2.44 (MTCK)
NEOPIX_PWR: LED1.2 (VDD), X2.43 (IO38)
RX: JP3.1, JP3.1C (1), X2.22 (XTAL_32K_N)
SCK: JP3.2, JP3.2C (2), X2.41 (IO36)
SCL: JP1.6, JP1.6C (6), X2.11 (IO6)
SCL1: CONN1.4 (SCL), X2.45 (MTD0)
SDA: JP1.5, JP1.5C (5), X2.12 (IO7)
SDA1: CONN1.3 (SDA), X2.47 (MTDI)
TX: JP1.7, JP1.7C (7), X2.10 (IO5)
TX00: X2.49 (U0TXD)
VBAT: D2.A, VBAT.P$1
VBUS: D1.A, X6.A4B9 (VBUS), X6.B4A9 (VBUS)
VDD3P3: C4.1, L1.2, X2.2 (VDD3P3), X2.3 (VDD3P3)
VDD_SPI: C12.1, C13.1, X2.29 (VDD_SPI)

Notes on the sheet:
Adafruit QT Py
http://adafruit.com/products/xxx
CC 2.5 BY-SA
NeoPixel
Stemma QT
3.3V LDO
USB Power/Data
Headers
Fast SPI No ADC
